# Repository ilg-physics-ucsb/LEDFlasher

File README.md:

# LEDFlasher

This repository is intended to hold all files related to the LED Flasher used in the oscilloscope lab, as well as instructions for creating building the device. The LED flasher is a simple circuit designed to flash an alternating pair of LEDs on and off with a BNC output to be read by an oscilloscope. It needs a center positive barrel jack power supply outputting between 5VDC and 24VDC.

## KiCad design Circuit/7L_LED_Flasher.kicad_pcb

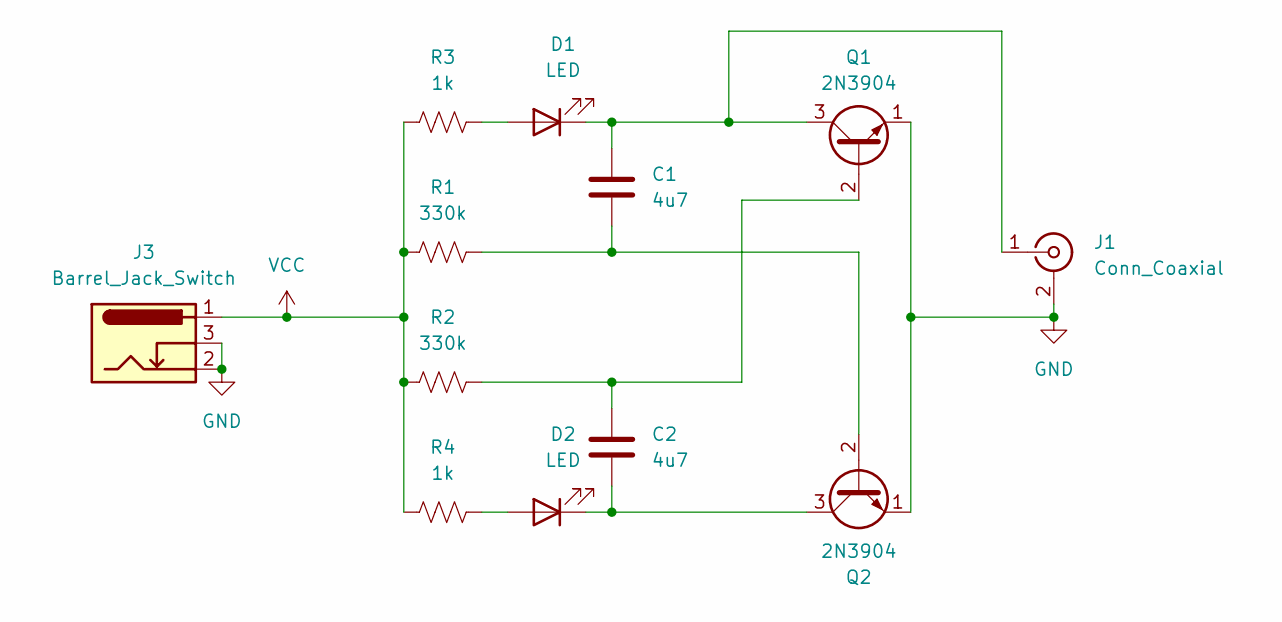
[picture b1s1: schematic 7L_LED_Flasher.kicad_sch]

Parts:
C1, C2: 4u7; C_Radial_D6.3mm_H7.0mm_P2.50mm
D1, D2: LED; LED_D5.0mm_Clear
J1: Conn_Coaxial; BNC_Amphenol_B6252HB-NPP3G-50_Horizontal
J3: Barrel_Jack_Switch; BarrelJack_GCT_DCJ200-10-A_Horizontal
Q1, Q2: 2N3904; TO-92_Inline_Wide
R1, R2: 330k; R_Axial_DIN0207_L6.3mm_D2.5mm_P10.16mm_Horizontal
R3, R4: 1k; R_Axial_DIN0207_L6.3mm_D2.5mm_P10.16mm_Horizontal

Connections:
GND: J1.2 (Ext), J3.2, J3.3, Q1.1 (E), Q2.1 (E)
unnamed: D1.2 (A), R3.2
unnamed: C1.2, D1.1 (K), J1.1 (In), Q1.3 (C)
unnamed: D2.2 (A), R4.2
unnamed: C2.1, D2.1 (K), Q2.3 (C)
unnamed: C2.2, Q1.2 (B), R2.2
unnamed: C1.1, Q2.2 (B), R1.2
VCC: J3.1, R1.1, R2.1, R3.1, R4.1

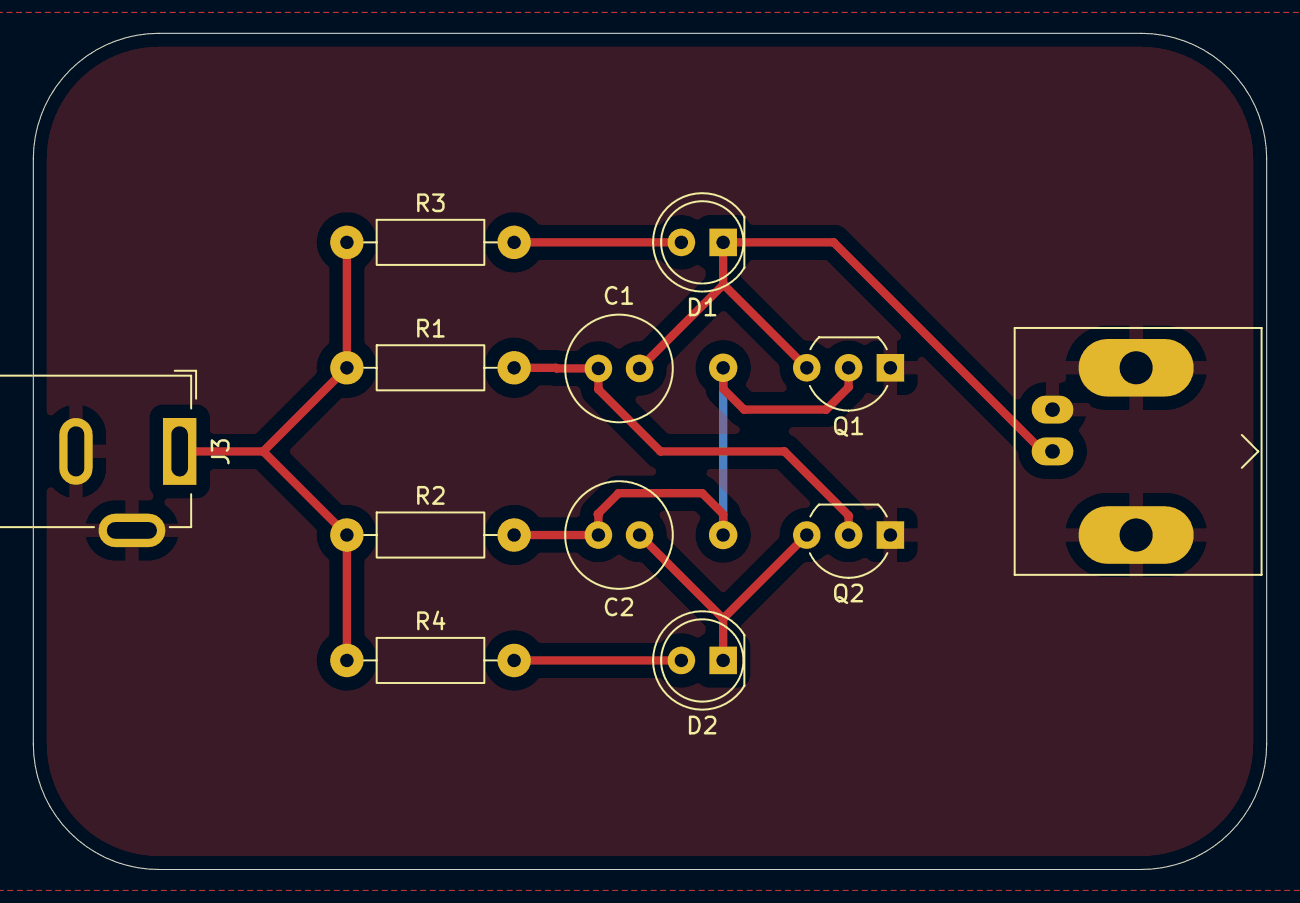
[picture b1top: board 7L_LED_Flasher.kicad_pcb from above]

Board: 2 copper layers, 74.9 x 50.8 mm, 12 parts (0 on the bottom side), 8 nets.

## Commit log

2026-02-19 Init repo
